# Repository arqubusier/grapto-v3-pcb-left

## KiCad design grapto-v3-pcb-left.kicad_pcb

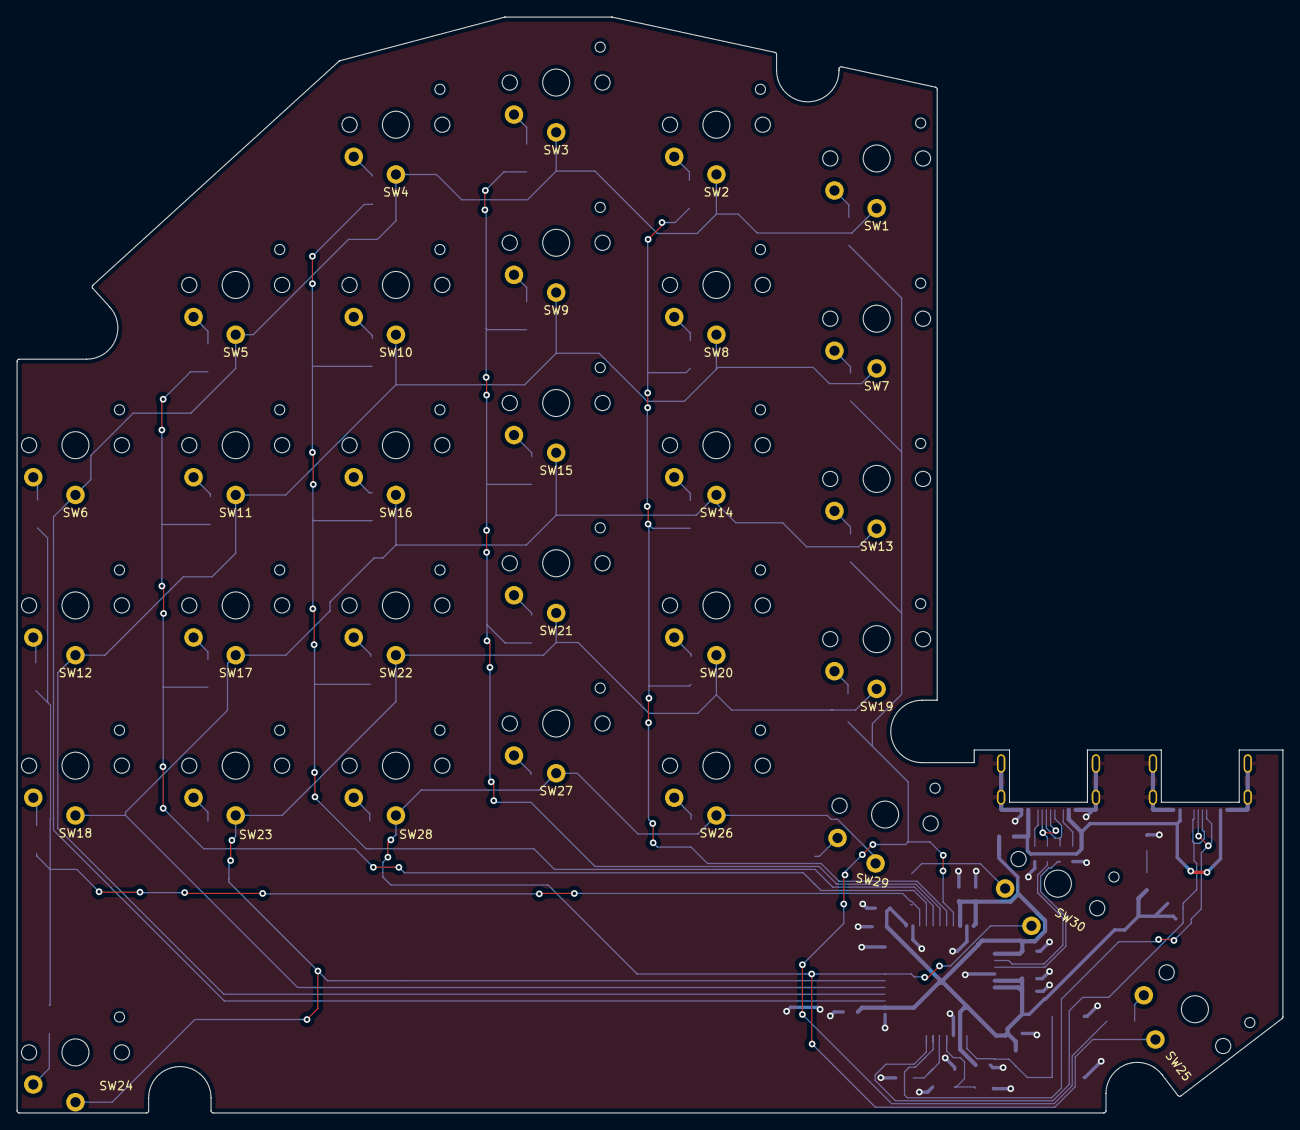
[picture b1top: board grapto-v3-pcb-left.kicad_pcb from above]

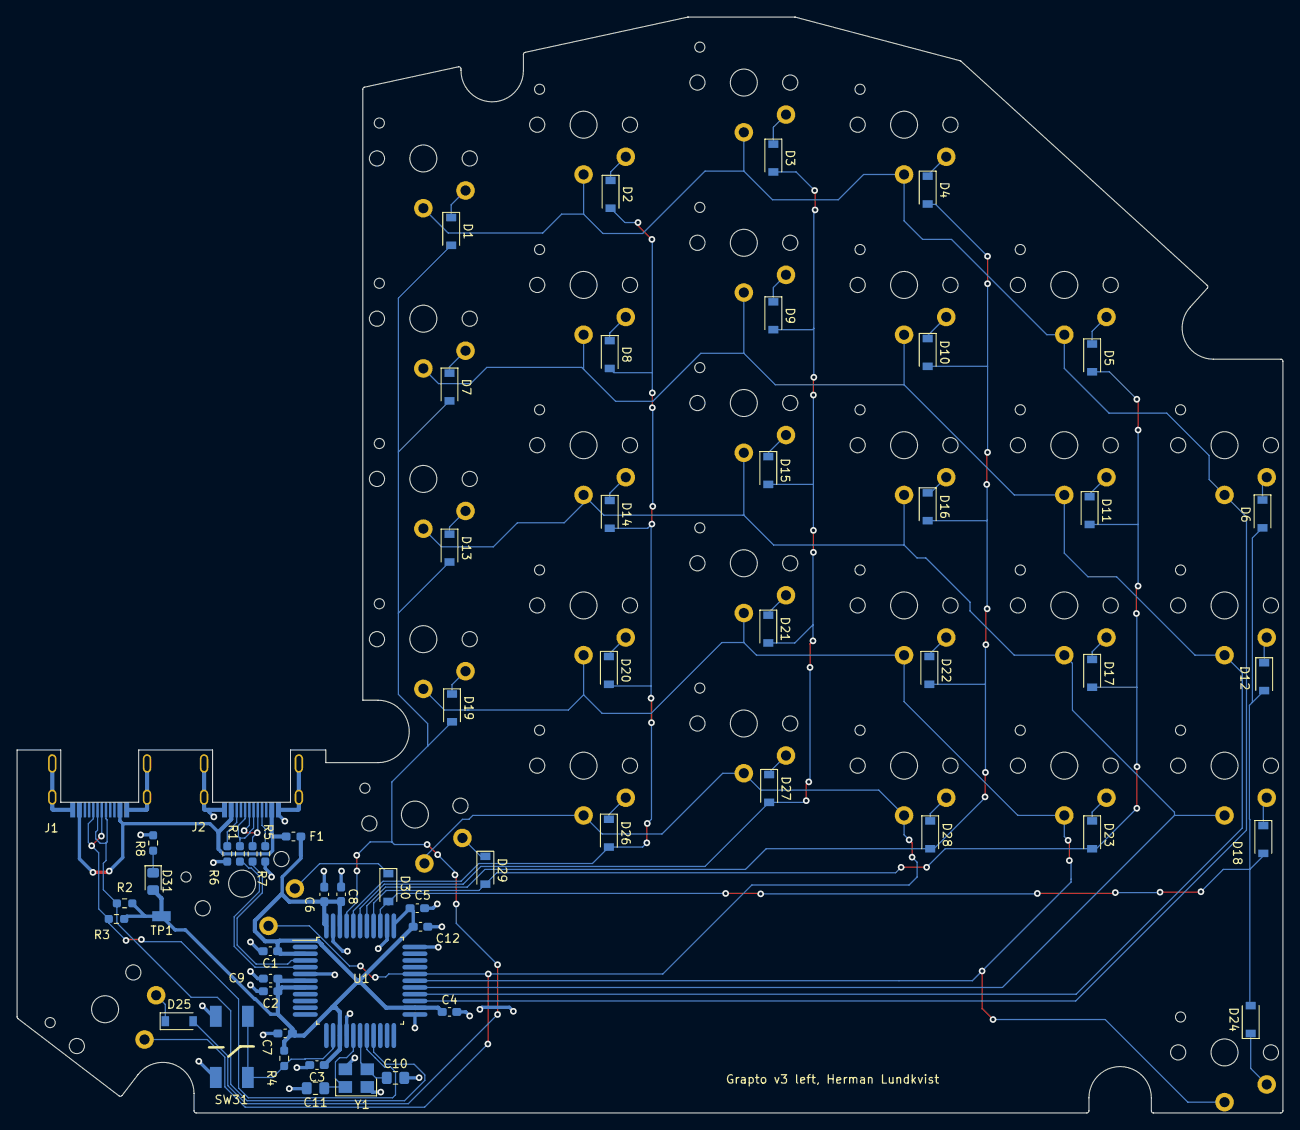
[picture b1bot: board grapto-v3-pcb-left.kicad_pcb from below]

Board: 2 copper layers, 150.1 x 129.9 mm, 88 parts (58 on the bottom side), 56 nets.

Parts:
C1, C2, C3, C4, C5, C6, C8: .1u; C_0603_1608Metric_Pad1.08x0.95mm_HandSolder
C7, C9, C12: 1u; C_0603_1608Metric_Pad1.08x0.95mm_HandSolder
C10, C11: 32p; C_0805_2012Metric_Pad1.18x1.45mm_HandSolder
D1, D2, D3, D4, D5, D6, D7, D8, D9, D10, D11, D12, D13, D14, D15, D16, D17, D18, D19, D20, D21, D22, D23, D24, D25, D26, D27, D28, D29, D30: D; D_SOD-123
D31: LED; D_0805_2012Metric_Pad1.15x1.40mm_HandSolder
F1: 200m; Fuse_0603_1608Metric_Pad1.05x0.95mm_HandSolder
J1, J2: USB_C_Receptacle_USB2.0; Connector_GCT_USB4500
R1, R7: 22; R_0603_1608Metric_Pad0.98x0.95mm_HandSolder
R2, R3: 1.2k; R_0603_1608Metric_Pad0.98x0.95mm_HandSolder
R4: 4.7k; R_0603_1608Metric_Pad0.98x0.95mm_HandSolder
R5, R6: 5.1k; R_0603_1608Metric_Pad0.98x0.95mm_HandSolder
R8: 68; R_0603_1608Metric_Pad0.98x0.95mm_HandSolder
SW1, SW2, SW3, SW4, SW5, SW6, SW7, SW8, SW9, SW10, SW11, SW12, SW13, SW14, SW15, SW16, SW17, SW18, SW19, SW20, SW21, SW22, SW23, SW24, SW25, SW26, SW27, SW28, SW29, SW30: SW_Push; SW_Kailh_Choc_V1
SW31: SW_SPST; Switch_TL3315NF100Q
TP1: TestPoint; TestPoint_S2761-46R
U1: ATmega32U4-AU; QFP-44_10x10_Pitch0.8mm_Hand_solder
Y1: Crystal_GND24; Crystal_ECS-160-20-33-TR3

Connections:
0V: C1.2, C2.2, C3.2, C4.2, C5.2, C6.2, C7.2, C8.2, C9.2, C10.2, C11.2, C12.2, J1.A12, J1.B12, J1.S1, J2.A12, J2.B12, J2.S1, R5.1, R6.1, R8.2, SW31.2, U1.5, U1.15, U1.23, U1.33, U1.35, U1.43, Y1.2, Y1.4
5V: C1.1, C2.1, C3.1, C4.1, C5.1, C6.1, C7.1, C8.1, C9.1, C12.1, D31.2, F1.1, R2.1, R3.1, R4.1, TP1.1, U1.2, U1.6, U1.7, U1.14, U1.24, U1.34, U1.42, U1.44
/Sheet61884E9A/SCL: J1.A6, J1.B6, R3.2, U1.18
/Sheet61884E9A/SDA: J1.A7, J1.B7, R2.2, U1.19
/Sheet61884E9A/USB_FULL_N: R7.2, U1.3
/Sheet61884E9A/USB_FULL_N1: J2.A7, J2.B7, R7.1
/Sheet61884E9A/USB_FULL_P: R1.2, U1.4
/Sheet61884E9A/USB_FULL_P1: J2.A6, J2.B6, R1.1
/Sheet61884E9A/XTAL1: C10.1, U1.17, Y1.1
/Sheet61884E9A/XTAL2: C11.1, U1.16, Y1.3
/Sheet61884E9A/~RST: R4.2, SW31.1, U1.13
/Sheet6188018D/col0: D1.2, D7.2, D13.2, D19.2, D25.2, U1.41
/Sheet6188018D/col1: D2.2, D8.2, D14.2, D20.2, D26.2, U1.40
/Sheet6188018D/col2: D3.2, D9.2, D15.2, D21.2, D27.2, U1.39
/Sheet6188018D/col3: D4.2, D10.2, D16.2, D22.2, D28.2, U1.38
/Sheet6188018D/col4: D5.2, D11.2, D17.2, D23.2, D29.2, U1.37
/Sheet6188018D/col5: D6.2, D12.2, D18.2, D24.2, D30.2, U1.36
/Sheet6188018D/row0: SW1.1, SW2.1, SW3.1, SW4.1, SW5.1, SW6.1, U1.25
/Sheet6188018D/row1: SW7.1, SW8.1, SW9.1, SW10.1, SW11.1, SW12.1, U1.26
/Sheet6188018D/row2: SW13.1, SW14.1, SW15.1, SW16.1, SW17.1, SW18.1, U1.27
/Sheet6188018D/row3: SW19.1, SW20.1, SW21.1, SW22.1, SW23.1, SW24.1, U1.28
/Sheet6188018D/row4: SW25.1, SW26.1, SW27.1, SW28.1, SW29.1, SW30.1, U1.29
unnamed: D1.1, SW1.2
unnamed: D2.1, SW2.2
unnamed: D3.1, SW3.2
unnamed: D4.1, SW4.2
unnamed: D5.1, SW5.2
unnamed: D6.1, SW6.2
unnamed: D7.1, SW7.2
unnamed: D8.1, SW8.2
unnamed: D9.1, SW9.2
unnamed: D10.1, SW10.2
unnamed: D11.1, SW11.2
unnamed: D12.1, SW12.2
unnamed: D13.1, SW13.2
unnamed: D14.1, SW14.2
unnamed: D15.1, SW15.2
unnamed: D16.1, SW16.2
unnamed: D17.1, SW17.2
unnamed: D18.1, SW18.2
unnamed: D19.1, SW19.2
unnamed: D20.1, SW20.2
unnamed: D21.1, SW21.2
unnamed: D22.1, SW22.2
unnamed: D23.1, SW23.2
unnamed: D24.1, SW24.2
unnamed: D25.1, SW25.2
unnamed: D26.1, SW26.2
unnamed: D27.1, SW27.2
unnamed: D28.1, SW28.2
unnamed: D29.1, SW29.2
unnamed: D30.1, SW30.2
unnamed: D31.1, R8.1
unnamed: J2.A5, R5.2
unnamed: J2.B5, R6.2
VBUS: F1.2, J1.A4, J1.B4, J2.A4, J2.B4

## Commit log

2021-11-13 Copied files from grapto-v3-right.
2021-11-13 fixed board outline
2021-11-15 First schematic draft complete.
2021-11-15 update.
2021-11-18 Updated schematic.
2021-11-18 minor update
2021-11-19 Routed signals.
2021-11-20 First layout done
2021-11-20 Update silkscreen
2021-11-20 Update switch footprint.
